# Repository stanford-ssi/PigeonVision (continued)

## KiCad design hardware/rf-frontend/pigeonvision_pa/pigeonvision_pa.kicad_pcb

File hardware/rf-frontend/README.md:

# RF frontend

**Current plan:** [Yapogee S3](../yapogee-s3/README.md) SMA output → separate GRF5613 PA → final filter → antenna, initially at 1.28 GHz. Use **1 W average at the PA output** as the present gain-budget target; clean 1–2 W DVB-S2 output remains unqualified. Ethernet/E200 is the alternate source, connected one source at a time by SMA cable.

[Edit diagram](block-diagram.drawio) · [Yapogee signal and power plan](../yapogee-s3/README.md) · [Link budget](../../calculations/link-budget.xlsx)

Yapogee contains the ESP32-S3-WROOM-1U module, short U.FL link, input pad/balun, RFFC5072A converter, LFCN-1450+ filter and SPF5043Z driver with a 3 dB output pad. Its 3.70 GHz LO converts 2.42 GHz to 1.28 GHz and reverses the complex spectrum; transmit IQ conjugation or corresponding receiver handling is required. The baseline uses that onboard driver to feed the separate PA.

| Stage / reference plane | Current basis |
| --- | --- |
| PA input | Approximately +6.2 dBm average for the 1 W PA-output estimate; the Yapogee SMA output must also cover external interconnect loss |
| PA | GRF5613, EVB184 1240–1420 MHz reference tune |
| PA output | +30 dBm = 1 W planning target, before final filter and antenna coax |
| Final filter | LFCN-1500+ candidate; verify spectrum, insertion loss, RF power and temperature |
| E200 fallback | Measure source power and waveform peaks; fit attenuation as required for the PA input |

EVB184 typical gain interpolates to about 23.77 dB at 1280 MHz, so 30 − 23.77 ≈ +6.23 dBm PA input. The same tune's typical CW output P1dB is about +33.7 dBm there. Pulse-shaped QPSK and 8PSK have waveform-dependent peaks; these CW numbers do not establish clean 1 W modulated output. Measure crest factor, gain, MER/EVM, spectral regrowth and temperature, then set backoff. A 1 dB final-filter loss would leave approximately 0.79 W from a 1 W PA output, before antenna-coax loss.

The preferred mechanical concept remains a PA daughterboard soldered to a carrier GND contact area, with thermal vias through both boards and a TIM-coupled heatsink below the carrier. Preserve ground copper beneath the PA. Mounting geometry, contact area and heat rejection remain unverified. Two low-profile heatsink planning footprints and envelope models are available in the [project library](../libraries/README.md), targeting 12.7 mm total underside clearance.

The optional breakout interface is a planned four-circuit Molex **0430450418** Micro-Fit 3.0 connector. The same power/control signals are needed for the soldered module; its lands have not been defined. No PA connector or control wiring has been added to the carrier schematic.

| Connector pin | Signal | Planned connection |
| --- | --- | --- |
| 1 | 5V_RF | Switched carrier RF buck output |
| 2 | GND | Power return |
| 3 | PA bias/disable control | Pi-controlled; polarity and routing remain to be implemented |
| 4 | GND | Control return; common with pin 2 |

Yapogee castellation 13 returns a PA request to CM5 GPIO22 / J3.46 as an input. The Pi independently controls the RF buck through GPIO17 / J3.50 and **5V_RF_EN**. Carrier PCB routing, firmware and the separate connector-pin-3 control remain unfinished. Keep the **1.5 A / 7.5 W** PA planning allowance until loaded measurements are available. This supply is separate from Yapogee's 5V_MAIN input and local regulators. The TPS62933 IC's 3 A rating does not establish the assembled carrier rail's continuous thermal capacity. EVB184 reports approximately 309 mA quiescent current at 5 V, which is not the loaded maximum.

The PA board provides RF chokes, decoupling, matching, bias resistors, shutdown logic and a thermal path from the exposed pad. Its active-high enable interface should have a 10 kΩ pull-down and keep the PA off when the carrier is unpowered or the cable is disconnected. GRF5613 **VSHDN is high to disable**, so local circuitry must handle this polarity and VEN1 / VEN2 sequencing; do not connect the bias pins directly to a GPIO. Mute RF before changing PA bias or rail power. Use EVB184's layout and matching as the starting point; its distributed matching cannot be copied to an arbitrary stackup without review.

The existing RF divider remains **R14 = 51 kΩ, R21 = 1.5 kΩ, R22 = 10 kΩ**, giving 5.000 V nominal. At an assumed 125°C resistor temperature, ±1% initial tolerance, opposite ±100 ppm/°C drift, 0.816 V maximum feedback reference and 0.15 µA maximum feedback input current give a **5.283 V static upper corner**, above the GRF5613's **5.25 V** supply ceiling. Changing R21 to 0 Ω is a **4.880 V nominal candidate**, with a 5.155 V upper corner under the same assumptions. That change is not applied. These calculations exclude ripple, startup and load-release transients; PA supply compliance and RF performance at the lower voltage need measurement. See the RF regulator calculation in [Design Master](../../calculations/design-master.xlsx).

SMA input/output. The final filter follows the PA and must be selected for the actual output spectrum and power. It cannot repair distortion already produced by clipping. RF matching, supply compliance, loaded current, shutdown sequencing and heatsinking remain hardware work.

[GRF5613 datasheet](https://www.guerrilla-rf.com/includes/prodFiles/5613/GRF5613DS.pdf) · [GRF5613 EVB184 tune](https://www.guerrilla-rf.com/includes/prodFiles/5613/GRF5613%20EVB184%201240-1420%20MHz.pdf) · [LFCN-1500+](https://www.minicircuits.com/pdfs/LFCN-1500%2B.pdf) · [Molex 0430450418](https://www.digikey.com/en/products/detail/molex/0430450418/2467320)

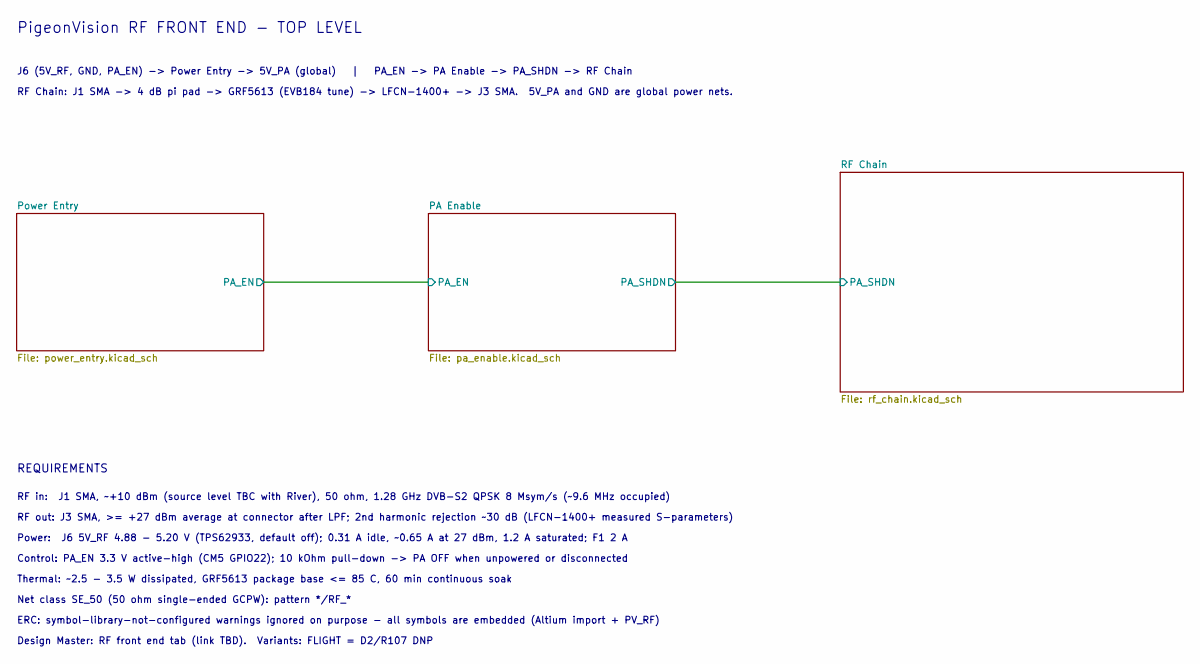
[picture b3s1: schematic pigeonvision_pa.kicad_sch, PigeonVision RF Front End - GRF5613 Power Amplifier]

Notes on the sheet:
Net class SE_50 (50 ohm single-ended GCPW): pattern */RF_*
Design Master: RF front end tab (link TBD). Variants: FLIGHT = D2/R107 DNP
Thermal: ~2.5 - 3.5 W dissipated, GRF5613 package base <= 85 C, 60 min continuous soak
Power: J6 5V_RF 4.88 - 5.20 V (TPS62933, default off); 0.31 A idle, ~0.65 A at 27 dBm, 1.2 A saturated; F1 2 A
REQUIREMENTS
PigeonVision RF FRONT END - TOP LEVEL
RF out: J3 SMA, >= +27 dBm average at connector after LPF; 2nd harmonic rejection ~30 dB (LFCN-1400+ measured S-parameters)
RF in: J1 SMA, ~+10 dBm (source level TBC with River), 50 ohm, 1.28 GHz DVB-S2 QPSK 8 Msym/s (~9.6 MHz occupied)
Control: PA_EN 3.3 V active-high (CM5 GPIO22); 10 kOhm pull-down -> PA OFF when unpowered or disconnected
RF Chain: J1 SMA -> 4 dB pi pad -> GRF5613 (EVB184 tune) -> LFCN-1400+ -> J3 SMA. 5V_PA and GND are global power nets.
ERC: symbol-library-not-configured warnings ignored on purpose - all symbols are embedded (Altium import + PV_RF)
J6 (5V_RF, GND, PA_EN) -> Power Entry -> 5V_PA (global) | PA_EN -> PA Enable -> PA_SHDN -> RF Chain

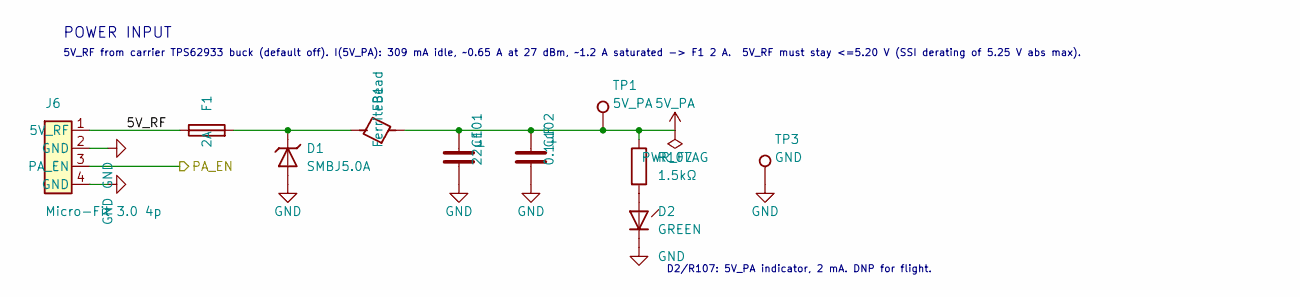
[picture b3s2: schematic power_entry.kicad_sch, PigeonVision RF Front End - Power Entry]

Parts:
C101: 22µF; C_1206_3216Metric; MPN TBD; LCSC TBD
C102: 0.1µF; C_0402_1005Metric; MPN GRM155R71C104KA88D; LCSC TBD
D1: SMBJ5.0A; D_SMB; MPN SMBJ5.0A; LCSC TBD
D2: GREEN; LED_0805_2012Metric; MPN LTST-C170KGKT; LCSC TBD
F1: 2A; Fuse_1206_3216Metric; MPN 0466002.NR; LCSC TBD
FB1: FerriteBead; L_1206_3216Metric; MPN TBD; LCSC TBD
J6: Micro-Fit 3.0 4p; Molex_Micro-Fit_3.0_43045-0418_2x02-1MP_P3.00mm_Vertical; MPN 0430450418; LCSC TBD
R107: 1.5kΩ; R_0402_1005Metric; MPN RC0402FR-071K5L; LCSC TBD
TP1: 5V_PA; TestPoint_Pad_D1.0mm
TP3: GND; TestPoint_Pad_D1.0mm

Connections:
5V_PA: C101.2, C102.2, FB1.2, R107.1, TP1.1 (1_1); also elsewhere on the board
/PA Enable/PA_EN: J6.3 (PA_EN); also elsewhere on the board
/Power Entry/5V_RF: F1.1, J6.1 (5V_RF)
GND: C101.1, C102.1, D1.2 (A), D2.1, J6.2 (GND), J6.4 (GND), TP3.1 (1_1); also elsewhere on the board
unnamed: D1.1 (K), F1.2, FB1.1
unnamed: D2.2, R107.2

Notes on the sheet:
POWER INPUT
5V_RF from carrier TPS62933 buck (default off). I(5V_PA): 309 mA idle, ~0.65 A at 27 dBm, ~1.2 A saturated -> F1 2 A. 5V_RF must stay <=5.20 V (SSI derating of 5.25 V abs max).
D2/R107: 5V_PA indicator, 2 mA. DNP for flight.

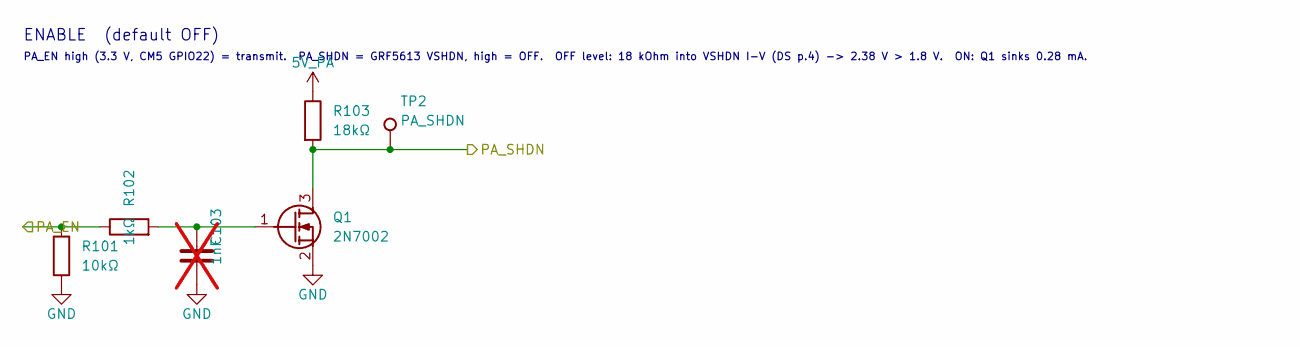
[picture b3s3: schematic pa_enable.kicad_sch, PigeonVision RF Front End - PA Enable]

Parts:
C103: 1nF; C_0402_1005Metric; MPN GRM155R71H102KA01D; LCSC TBD; not fitted
Q1: 2N7002; SOT-23; MPN 2N7002KT1G; LCSC TBD
R101: 10kΩ; R_0402_1005Metric; MPN RC0402FR-0710KL; LCSC TBD
R102: 1kΩ; R_0402_1005Metric; MPN RC0402FR-071KL; LCSC TBD
R103: 18kΩ; R_0402_1005Metric; MPN RC0402FR-0718KL; LCSC TBD
TP2: PA_SHDN; TestPoint_Pad_D1.0mm

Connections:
5V_PA: R103.1; also elsewhere on the board
/PA Enable/PA_EN: R101.1, R102.1; also elsewhere on the board
/PA Enable/PA_SHDN: Q1.3 (D), R103.2, TP2.1 (1_1); also elsewhere on the board
GND: C103.1, Q1.2 (S), R101.2; also elsewhere on the board
unnamed: C103.2, Q1.1 (G), R102.2

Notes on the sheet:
PA_EN high (3.3 V, CM5 GPIO22) = transmit. PA_SHDN = GRF5613 VSHDN, high = OFF. OFF level: 18 kOhm into VSHDN I-V (DS p.4) -> 2.38 V > 1.8 V. ON: Q1 sinks 0.28 mA.
ENABLE (default OFF)

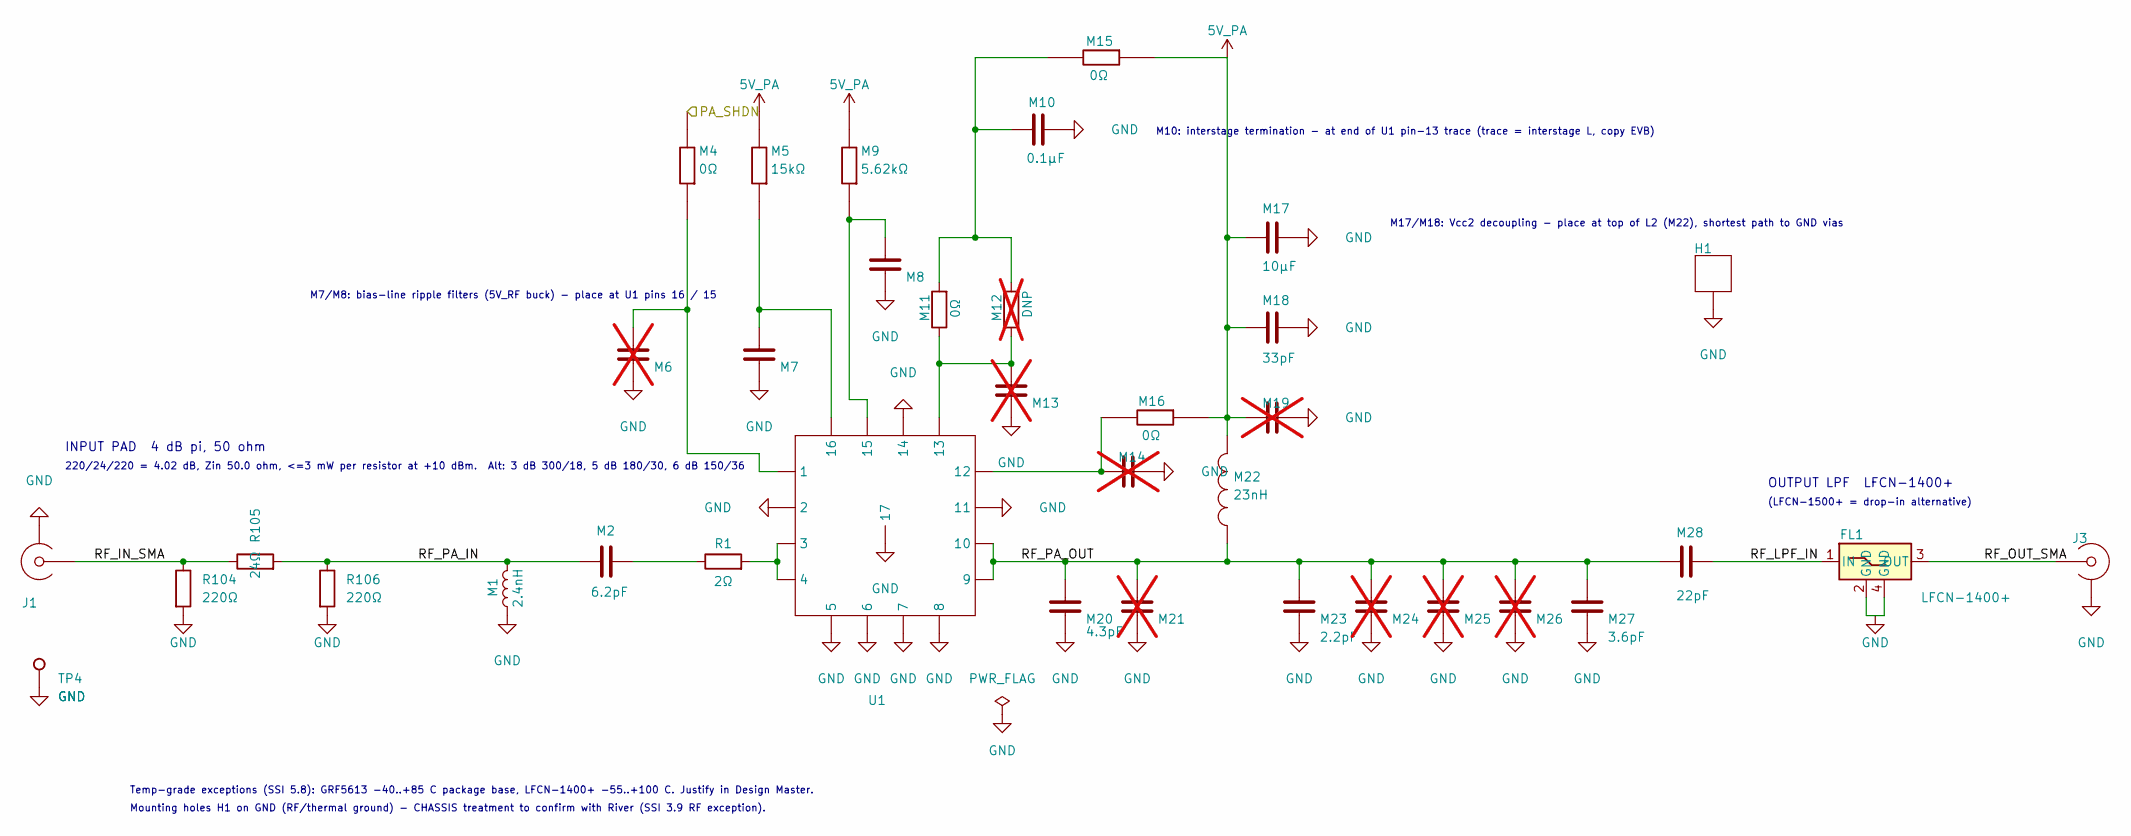
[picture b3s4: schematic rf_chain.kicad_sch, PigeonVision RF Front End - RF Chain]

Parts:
FL1: LFCN-1400+; MiniCircuits_FV1206_LFCN; MPN LFCN-1400+; LCSC TBD
H1: Heatsink; Heatsink_wFid
J1, J3: SMA; SMA Round_Pin_RevC; MPN TBD
M1: 2.4nH; 0402_20x26x22; MPN LQG15HS2N4S02D
M2: 6.2pF; 0402_20x30x18; MPN GJM1555C1H6R2BB01D
M4, M11, M15, M16: 0Ω; 0402_26x26x20; MPN RC0402JR-070RL
M5: 15kΩ; 0402_26x26x20; MPN RC0402FR-0715KL
M6, M13, M14, M19: DNP; 0402_20x26x16; not fitted
M7, M8, M10: 0.1µF; 0402_20x26x16; MPN GRM155R71C104KA88D
M9: 5.62kΩ; 0402_26x26x20; MPN RC0402FR-075K62L
M12: DNP; 0402_26x26x20; not fitted
M17: 10µF; 0402_20x26x16; MPN TBD
M18: 33pF; 0402_20x26x16; MPN GJM1555C1H330GB01D
M20: 4.3pF; 0402_20x26x22; MPN GJM1555C1H4R3BB01D
M21, M24, M25, M26: DNP; 0402_20x26x22; not fitted
M22: 23nH; 0603_26x40x30; MPN 0908SQ-23NGLC
M23: 2.2pF; 0402_20x26x22; MPN GJM1555C1H2R2BB01D
M27: 3.6pF; 0402_20x26x22; MPN GJM1555C1H3R6BB01D
M28: 22pF; 0402_20x30x18; MPN GJM1555C1H220GB01D
R1: 2Ω; R_0603_1608Metric; MPN RC0603FR-072RL
R104, R106: 220Ω; R_0402_1005Metric; MPN RC0402FR-07220RL; LCSC TBD
R105: 24Ω; R_0402_1005Metric; MPN RC0402FR-0724RL; LCSC TBD
TP4: GND; TestPoint_Pad_D1.0mm
U1: GRF5613; QFN16_3x3mm_RevG; MPN GRF5613

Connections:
5V_PA: M5.2, M9.2, M15.1, M16.1, M17.2, M18.2, M19.2, M22.2; also elsewhere on the board
/PA Enable/PA_SHDN: M4.2; also elsewhere on the board
/RF Chain/RF_IN_SMA: J1.1, R104.1, R105.1
/RF Chain/RF_LPF_IN: FL1.1 (IN), M28.1
/RF Chain/RF_OUT_SMA: FL1.3 (OUT), J3.1
/RF Chain/RF_PA_IN: M1.2, M2.2, R105.2, R106.1
/RF Chain/RF_PA_OUT: M20.2, M21.2, M22.1, M23.2, M24.2, M25.2, M26.2, M27.2, M28.2, U1.9, U1.10
GND: FL1.2 (GND), FL1.4 (GND), H1.1 (1_1), J1.2, J3.2, M1.1, M6.1, M7.1, M8.1, M10.1, M13.1, M14.1, M17.1, M18.1, M19.1, M20.1, M21.1, M23.1, M24.1, M25.1, M26.1, M27.1, R104.2, R106.2, TP4.1 (1_1), U1.2, U1.5, U1.6, U1.7, U1.8, U1.11, U1.14, U1.17; also elsewhere on the board
unnamed: M2.1, R1.1
unnamed: M4.1, M6.2, U1.1
unnamed: M5.1, M7.2, U1.16
unnamed: M8.2, M9.1, U1.15
unnamed: M10.2, M11.2, M12.2, M15.2
unnamed: M11.1, M12.1, M13.2, U1.13
unnamed: M14.2, M16.2, U1.12
unnamed: R1.2, U1.3, U1.4

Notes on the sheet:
M10: interstage termination - at end of U1 pin-13 trace (trace = interstage L, copy EVB)
(LFCN-1500+ = drop-in alternative)
M17/M18: Vcc2 decoupling - place at top of L2 (M22), shortest path to GND vias
M7/M8: bias-line ripple filters (5V_RF buck) - place at U1 pins 16 / 15
Temp-grade exceptions (SSI 5.8): GRF5613 -40..+85 C package base, LFCN-1400+ -55..+100 C. Justify in Design Master.
OUTPUT LPF LFCN-1400+
220/24/220 = 4.02 dB, Zin 50.0 ohm, <=3 mW per resistor at +10 dBm. Alt: 3 dB 300/18, 5 dB 180/30, 6 dB 150/36
INPUT PAD 4 dB pi, 50 ohm
Mounting holes H1 on GND (RF/thermal ground) - CHASSIS treatment to confirm with River (SSI 3.9 RF exception).

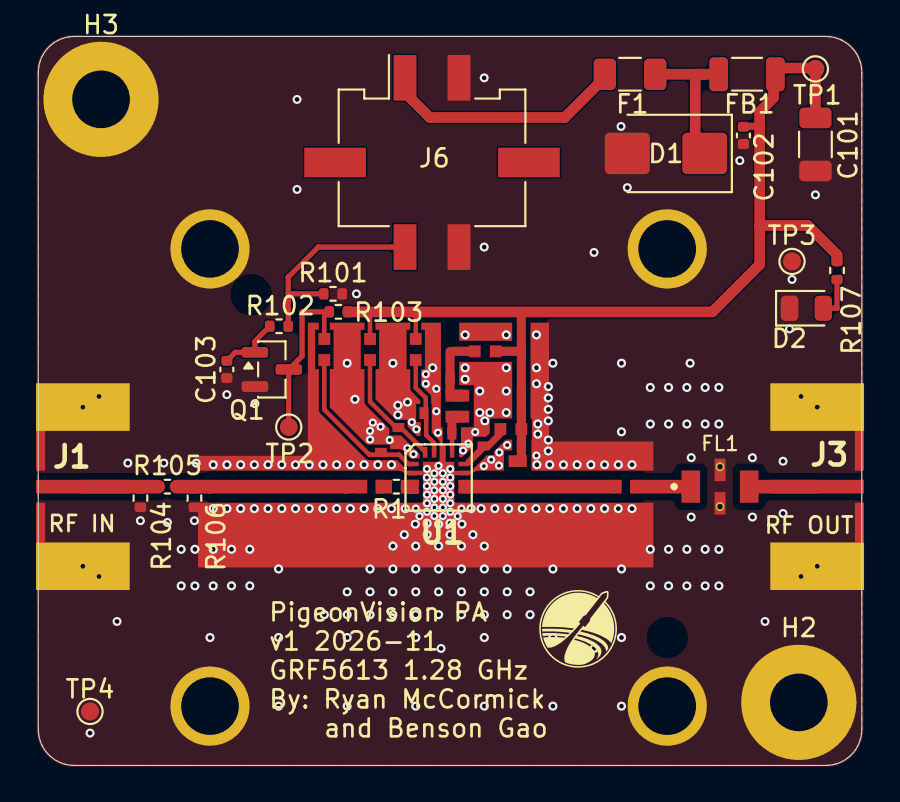
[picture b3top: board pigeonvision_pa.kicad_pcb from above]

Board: 2 copper layers, 45.8 x 40.5 mm, 55 parts (0 on the bottom side), 21 nets.

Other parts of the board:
H2, H3: MountingHole_Pad; MountingHole_3.2mm_M3_Pad

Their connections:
GND: H2.1 (1_1), H3.1 (1_1); also elsewhere on the board
